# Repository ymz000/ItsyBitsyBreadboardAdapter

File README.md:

### _A stacking breadboard adapter for the ItsyBitsy M4 Express_

# ItsyBitsyBreadboardAdapter

## Overview
The ItsyBitsy Breadboard Adapter is an Adafruit ItsyBitsy M4 Express-compatible piggyback module that converts the 3-sided pinout of the ItsyBitsy to dual in-line for use on typical solderless breadboards and soldered protoboards. The adapter was also designed with extra solderable pin connections and mounting ears for permanent installation.

Included is a level-shifted 4-pin JST STEMMA connector with jumper-selectable 5v or 3.3v power. The STEMMA interface can be configured to connect to the ItsyBitsy's UART (RX/TX) or I2C (SCL/SDA) signals. A 2-pin JST LiPo battery connection is on-board that supports charging (100mA charge rate), compatible with Adafruit's standard battery polarity.

OSH Park shared project: <a href="https://oshpark.com/shared_projects/2K1V8CQO"></img></a>

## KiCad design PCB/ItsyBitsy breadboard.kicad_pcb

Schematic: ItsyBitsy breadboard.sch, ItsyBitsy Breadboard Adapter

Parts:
C1: 10uF; C_0805
D1: ORG; LED_0805
D2: GRN; LED_0805
J1: EDGE PINS; Pin_Header_Straight_1x17_Pitch2.54mm_no_silk
J2, J8: EDGE PINS; Pin_Header_Straight_1x16_Pitch2.54mm_no_silk
J4: STEMMA; JST_PH_B4B-PH-K_04x2.00mm_Straight
J5: BATTERY; JST_PH_B2B-PH-K_02x2.00mm_Straight
J6: XTRA; Pin_Header_Straight_1x05_Pitch2.54mm_no_silk
J7: BODGE PINS; Pin_Header_Straight_1x17_Pitch2.54mm_no_silk
JMP1: SCL_RX; GS3
JMP2: SDA_TX; GS3
JMP3: Vbat; GS2
JMP4: STEMMA_VOLTS; GS3
M1: ItsyBitsy_M4_Express
Q1: BSS138DW-7-F; SOT-363; MPN BSS138DW-7-F; Digi-Key_PN BSS138DW-FDICT-ND
R1, R2: 1.5K; R_0805
R3, R5: 100K; R_0805
R4: 10K; R_0805
RN1: 4x10K; R_Array_Convex_4x0603
U1: MCP73831-2-OT; SOT-23-5

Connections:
+3V3: J1.2, J4.3, J7.2, JMP4.2, JMP4.3, Q1.2, Q1.5, R2.1, RN1.1, RN1.2, RN1.3, RN1.4
/A2: J1.7, J7.7
/A3: J1.8, J7.8
/A4: J1.9, J7.9
/A5: J1.10, J7.10
/Aref: J1.3, J7.3
/BAT: C1.1, J2.1, J5.1, J8.1, R3.1, U1.3 (Vbat)
/D0-RX: J2.14, J8.14, JMP1.3
/D1-TX: J2.13, J8.13, JMP2.3
/D2-A6: J1.14, J7.14, JMP3.1
/D3: J2.16, J6.4, J8.16
/D4: J2.15, J6.5, J8.15
/D5!: J2.10, J8.10
/D7: J2.9, J8.9
/D9: J2.8, J8.8
/D10: J2.7, J8.7
/D11: J2.6, J8.6
/D12: J2.5, J8.5
/D13-LED: J2.4, J8.4
/En: J1.15, J6.1, J7.15
/MI: J1.13, J7.13
/MO: J1.12, J7.12
/SCK: J1.11, J7.11
/SCL: J2.11, J8.11, JMP1.1, JMP1.2, Q1.4, RN1.6
/SDA: J2.12, J8.12, JMP2.1, JMP2.2, Q1.1, RN1.7
/STEMMA_SCL: J4.1, Q1.3, RN1.5
/STEMMA_SDA: J4.2, Q1.6, RN1.8
/USB: D1.2, J2.3, J8.3, U1.4 (Vdd)
/Vhi: J1.4, J7.4, JMP4.1
/swclk: J1.17, J6.3, J7.17
/swdio: J1.16, J6.2, J7.16
/~RST: J1.1, J7.1
/~~A0: J1.5, J7.5
/~~A1: J1.6, J7.6
GND: C1.2, D2.1, J2.2, J4.4, J5.2, J8.2, R4.2, R5.2, U1.2 (Vss)
unnamed: D1.1, R1.1
unnamed: D2.2, R2.2
unnamed: JMP3.2, R3.2, R5.1
unnamed: R1.2, U1.1 (STAT)
unnamed: R4.1, U1.5 (PROG)

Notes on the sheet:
STEMMA Interface
Battery
100mA CHARGE RATE
POWER
BATTERY MANAGEMENT
Defaults to +3.3V

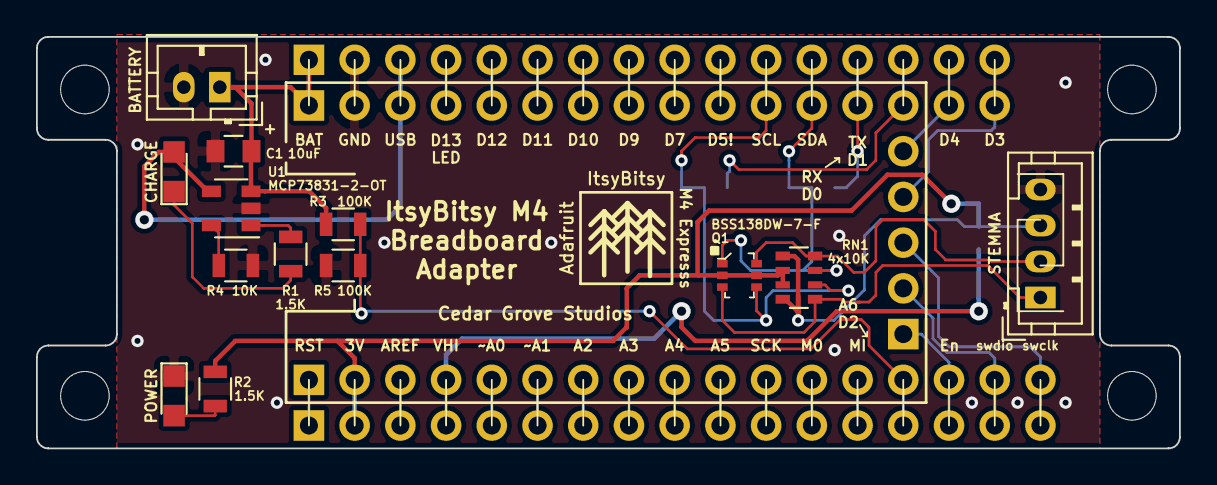
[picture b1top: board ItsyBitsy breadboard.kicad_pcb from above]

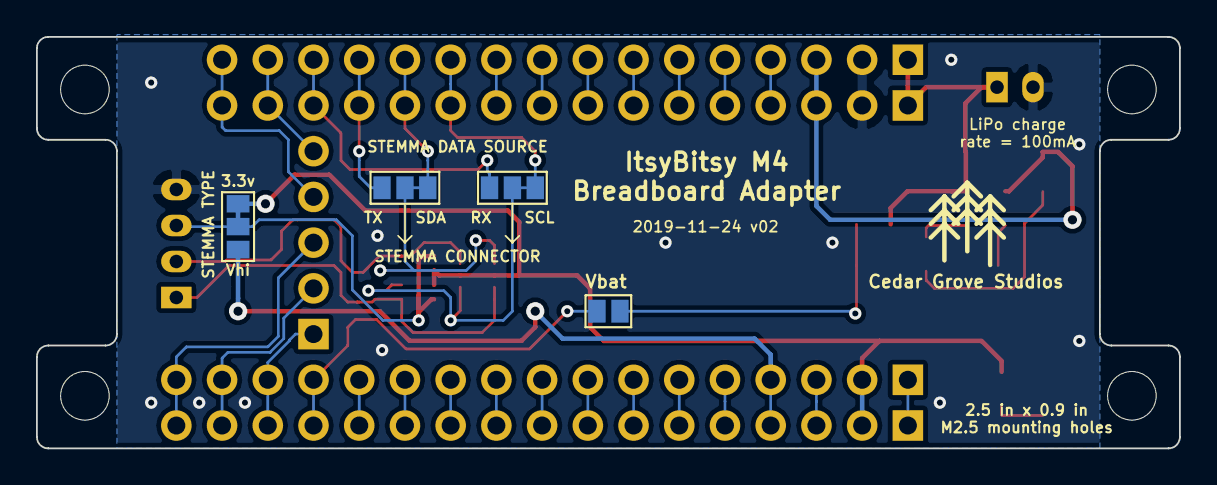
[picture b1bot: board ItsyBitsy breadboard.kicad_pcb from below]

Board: 2 copper layers, 63.5 x 22.9 mm, 22 parts (4 on the bottom side), 40 nets.

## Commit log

2019-04-28 Initial repository load
2019-04-28 updated to include hardware designs
2019-04-28 old version
2019-11-22 collect circuit ideas for next version
2019-11-25 update with new design and photos
2019-11-25 update footprint
2019-11-25 update design and layout
2019-11-25 update renderings
2019-11-25 Update STEMMA type default
2019-11-25 update circuit design
2019-11-25 update charging design
2019-12-18 add assembled and tested photos
2019-12-18 update oshpark link
2019-12-18 update charging LED resistor
2019-12-18 add default Stemma jumpers
2019-12-19 update PCB silkscreen
